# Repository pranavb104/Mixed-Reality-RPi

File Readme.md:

## About

A Mixed-Reality device using the small yet powerful RPI Zero 2W。It detect fiducials (aruco-markers) via the RPI dedicated camera and plays 720p resolution videos when detected. All of this running simulataneously on the PI Zero2W.This device gives a unique way to interact with static content as opposed to viewing it from screens which can be bulky and expensive to setup. This experience could also make way for interactive games and other kind of explorative projects.

I've compiled this project in Openframeworks (OFv0.10.0). It was difficult to link the libraries, especially to compile ofxOMXPlayer and ofxOMXCamera. So, ill provide a detailed guide for the right environment and setup instructions. This project greatly relies on the work done by [jvcleave](https://github.com/jvcleave/ofxOMXCamera) for building the OMX wrapper inside openframeworks. 

## Instructions 
Before downloading the source files, make sure you have your environment setup:
RPI Buster 5.10.17 armv7l
OFv0.10.0

Then download the dependent libraries which are:
ofxAruco
ofxCv
ofxOpenCv
ofxPoco
ofxOMXCamera
ofxOMXPlayer

Before compiling, you would need to make certain changes in your config file located in:
libs/openFrameworksCompiled/project/linuxarmv6l/config.linuxarmv6l.default.mk

Comment out: USE_GLFW_WINDOW = 1 AND USE_PI_LEGACY = 0

And then Add PROJECT_LDFLAGS += -latomic to file: config.make for your project to compile.

## KiCAD PCB

This PCB builds upon the work done by [mickmakes](https://github.com/MickMake/Project-PiProjector). It uses a simple charging circuit, along with outputs to detect the battery health and other charging paramters. I've also uploaded the BOM for sourcing the components. However some components like the MCP23008, TPS61030PWP & MCP73871 are not mentioned, since due to chip shortage these need to be sourced from other local Chinese vendors on [Taobao](http://taobao.com). Otherwise they are easily available on Mouser or Digikey.

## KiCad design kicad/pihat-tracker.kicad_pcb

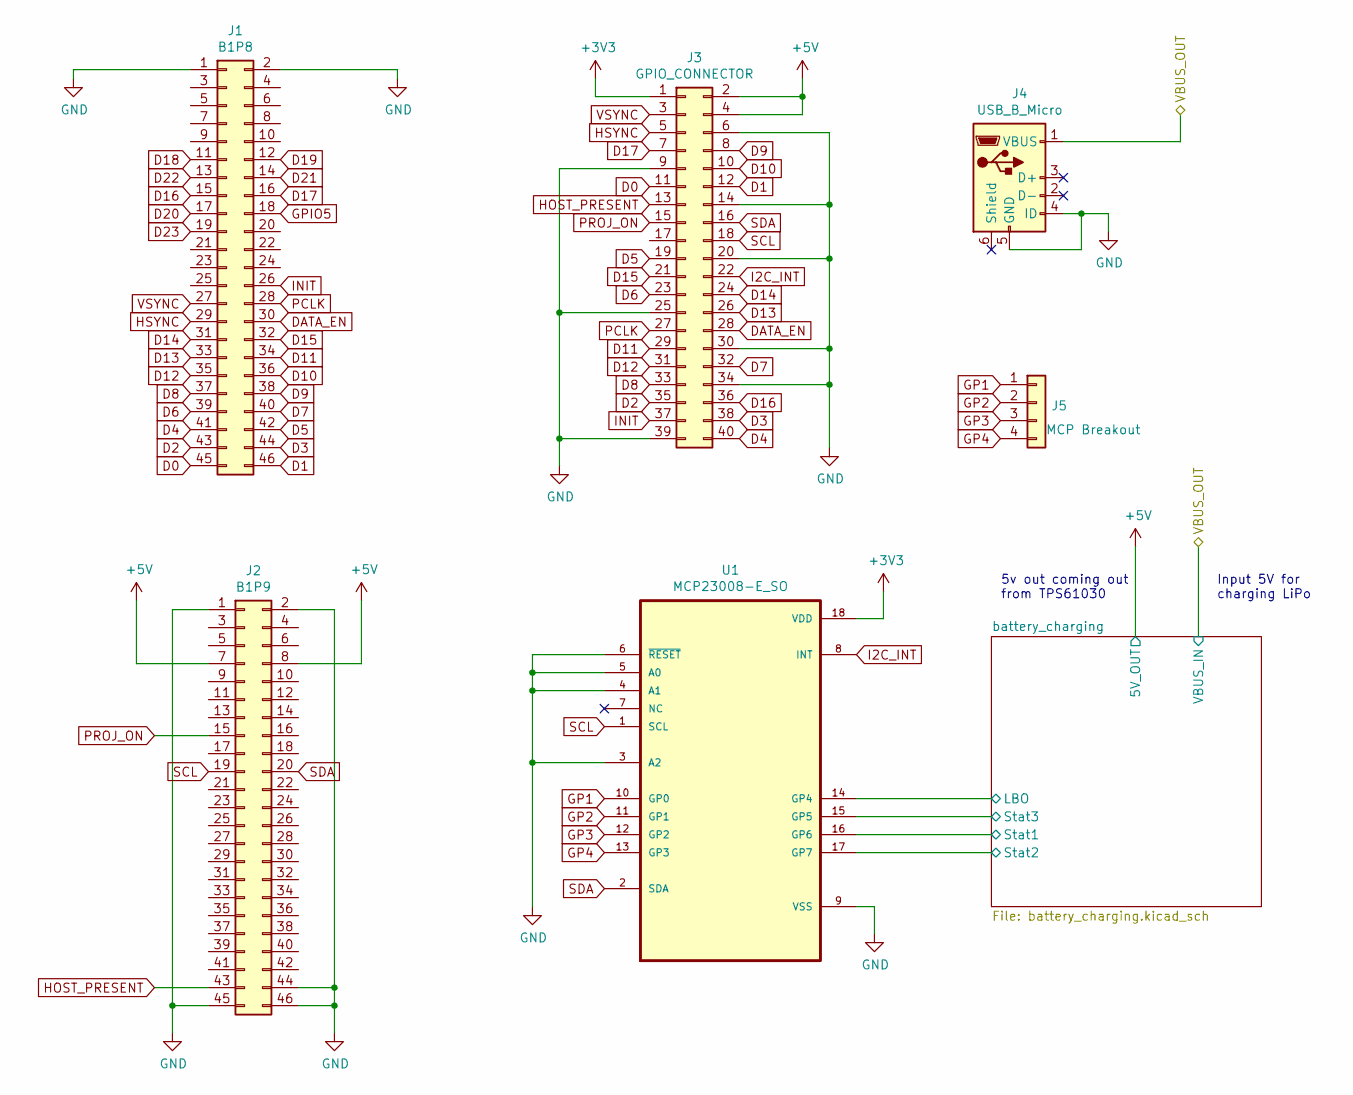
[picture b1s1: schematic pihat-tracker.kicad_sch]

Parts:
J1: B1P8; PinHeader_2x23_P2.54mm_Vertical
J2: B1P9; PinHeader_2x23_P2.54mm_Vertical
J3: GPIO_CONNECTOR; Raspberry_Pi_Zero_Socketed_THT_FaceDown_MountingHoles
J4: USB_B_Micro; USB_Micro-B_Molex-105017-0001
J5: MCP Breakout; PinHeader_1x04_P2.54mm_Vertical
U1: MCP23008-E_SO; SOIC127P1030X265-18N

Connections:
+3V3: J3.1, U1.18 (VDD)
+5V: J2.7, J2.8, J3.2, J3.4; also elsewhere on the board
/VBUS_OUT: J4.1 (VBUS); also elsewhere on the board
/battery_charging/LBO: U1.14 (GP4); also elsewhere on the board
/battery_charging/Stat1: U1.16 (GP6); also elsewhere on the board
/battery_charging/Stat2: U1.17 (GP7); also elsewhere on the board
/battery_charging/Stat3: U1.15 (GP5); also elsewhere on the board
D0: J1.45, J3.11
D1: J1.46, J3.12
D2: J1.43, J3.35
D3: J1.44, J3.38
D4: J1.41, J3.40
D5: J1.42, J3.19
D6: J1.39, J3.23
D7: J1.40, J3.32
D8: J1.37, J3.33
D9: J1.38, J3.8
D10: J1.36, J3.10
D11: J1.34, J3.29
D12: J1.35, J3.31
D13: J1.33, J3.26
D14: J1.31, J3.24
D15: J1.32, J3.21
D16: J1.15, J3.36
D17: J1.16, J3.7
D18: J1.11
D19: J1.12
D20: J1.17
D21: J1.14
D22: J1.13
D23: J1.19
DATA_EN: J1.30, J3.28
GND: J1.1, J1.2, J2.1, J2.2, J2.44, J2.45, J2.46, J3.6, J3.9, J3.14, J3.20, J3.25, J3.30, J3.34, J3.39, J4.4 (ID), J4.5 (GND), U1.3 (A2), U1.4 (A1), U1.5 (A0), U1.6 (~RESET), U1.9 (VSS); also elsewhere on the board
GP1: J5.1, U1.10 (GP0)
GP2: J5.2, U1.11 (GP1)
GP3: J5.3, U1.12 (GP2)
GP4: J5.4, U1.13 (GP3)
GPIO5: J1.18
HOST_PRESENT: J2.43, J3.13
HSYNC: J1.29, J3.5
I2C_INT: J3.22, U1.8 (INT)
INIT: J1.26, J3.37
PCLK: J1.28, J3.27
PROJ_ON: J2.15, J3.15
SCL: J2.19, J3.18, U1.1 (SCL)
SDA: J2.20, J3.16, U1.2 (SDA)
VSYNC: J1.27, J3.3

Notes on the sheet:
5v out coming out from TPS61030
Input 5V for charging LiPo

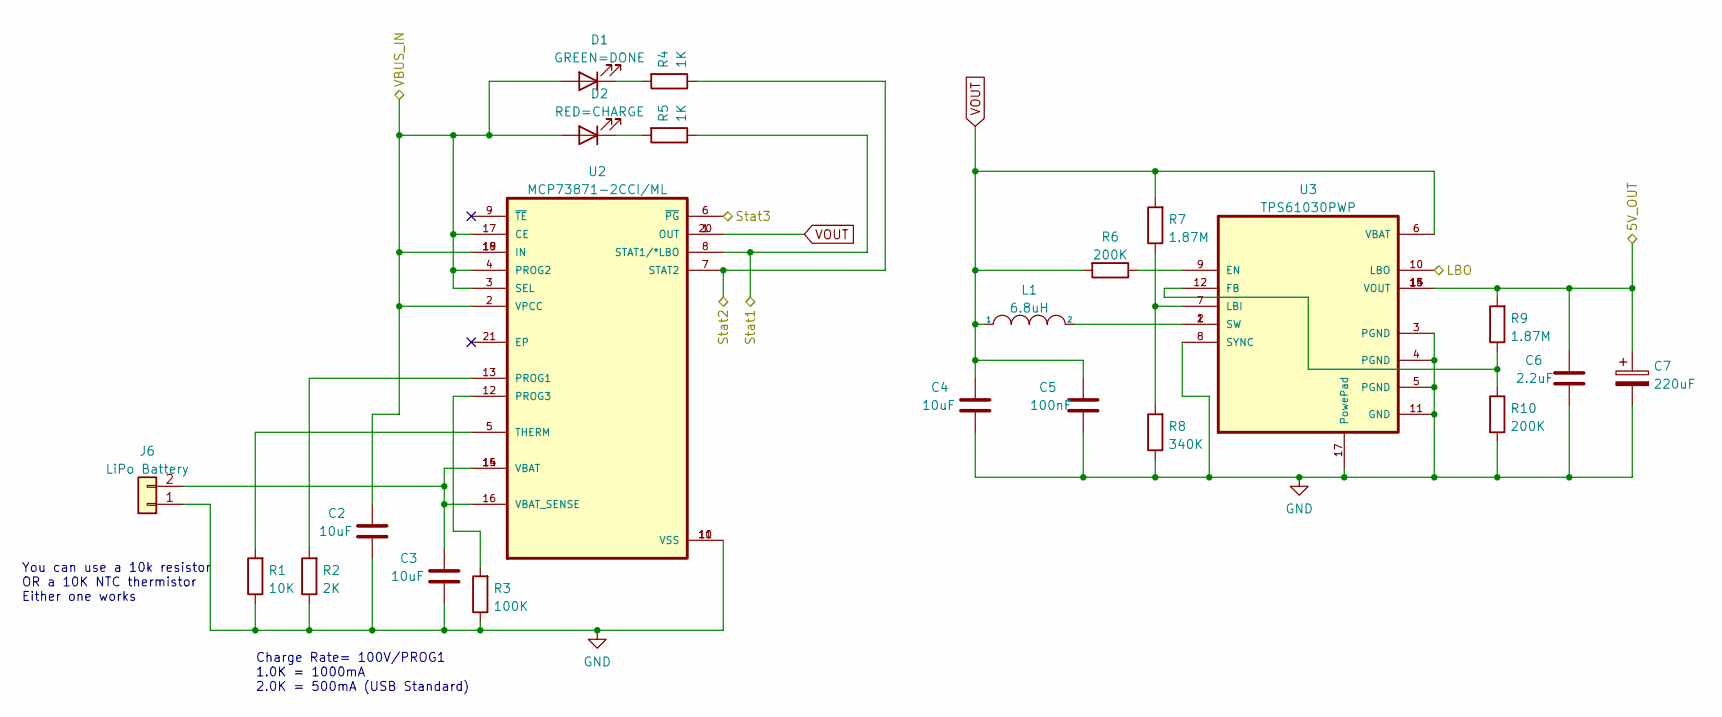
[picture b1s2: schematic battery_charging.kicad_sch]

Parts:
C2, C3, C4: 10uF; C_1206_3216Metric
C5: 100nF; C_1206_3216Metric
C6: 2.2uF; C_1206_3216Metric
C7: 220uF; CP_Elec_6.3x7.7
D1: GREEN=DONE; LED_1206_3216Metric
D2: RED=CHARGE; LED_1206_3216Metric
J6: LiPo Battery; PinHeader_1x02_P2.54mm_Vertical
L1: 6.8uH; L_Bourns-SRN8040_8x8.15mm
R1: 10K; R_1206_3216Metric
R2: 2K; R_1206_3216Metric
R3: 100K; R_1206_3216Metric
R4, R5: 1K; R_1206_3216Metric
R6, R10: 200K; R_1206_3216Metric
R7, R9: 1.87M; R_1206_3216Metric
R8: 340K; R_1206_3216Metric
U2: MCP73871-2CCI/ML; QFN50P400X400X100-21N
U3: TPS61030PWP; SOP65P640X120-17N

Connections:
+5V: C6.1, C7.1, R9.2, U3.13 (VOUT), U3.14 (VOUT), U3.15 (VOUT); also elsewhere on the board
/VBUS_OUT: C2.1, D1.2 (A), D2.2 (A), U2.2 (VPCC), U2.3 (SEL), U2.4 (PROG2), U2.17 (CE), U2.18 (IN), U2.19 (IN); also elsewhere on the board
/battery_charging/LBO: U3.10 (LBO); also elsewhere on the board
/battery_charging/Stat1: R5.1, U2.8 (STAT1/*LBO); also elsewhere on the board
/battery_charging/Stat2: R4.1, U2.7 (STAT2); also elsewhere on the board
/battery_charging/Stat3: U2.6 (~PG); also elsewhere on the board
GND: C2.2, C3.2, C4.2, C5.2, C6.2, C7.2, J6.1, R1.1, R2.1, R3.1, R8.1, R10.2, U2.10 (VSS), U2.11 (VSS), U3.3 (PGND), U3.4 (PGND), U3.5 (PGND), U3.8 (SYNC), U3.11 (GND), U3.17 (PowePad); also elsewhere on the board
unnamed: C3.1, J6.2, U2.14 (VBAT), U2.15 (VBAT), U2.16 (VBAT_SENSE)
unnamed: D1.1 (K), R4.2
unnamed: D2.1 (K), R5.2
unnamed: L1.2, U3.1 (SW), U3.2 (SW)
unnamed: R1.2, U2.5 (THERM)
unnamed: R2.2, U2.13 (PROG1)
unnamed: R3.2, U2.12 (PROG3)
unnamed: R6.1, U3.9 (EN)
unnamed: R7.1, R8.2, U3.7 (LBI)
unnamed: R9.1, R10.1, U3.12 (FB)
VOUT: C4.1, C5.1, L1.1, R6.2, R7.2, U2.1 (OUT), U2.20 (OUT), U3.6 (VBAT)

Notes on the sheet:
Charge Rate= 100V/PROG1 1.0K = 1000mA 2.0K = 500mA (USB Standard)
You can use a 10k resistor OR a 10K NTC thermistor Either one works

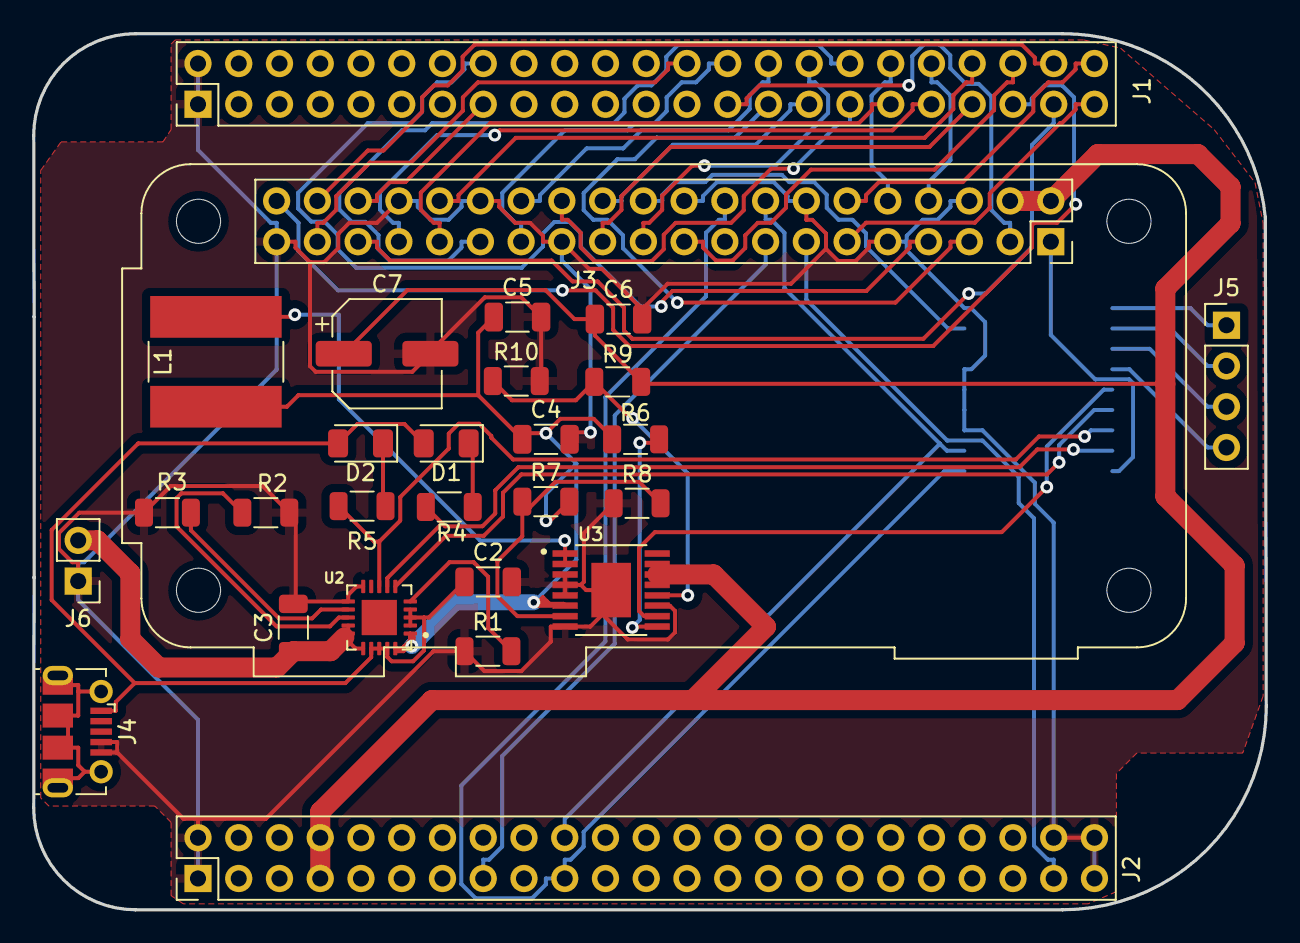
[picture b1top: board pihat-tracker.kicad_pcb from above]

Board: 2 copper layers, 76.8 x 54.6 mm, 28 parts (1 on the bottom side), 51 nets.
